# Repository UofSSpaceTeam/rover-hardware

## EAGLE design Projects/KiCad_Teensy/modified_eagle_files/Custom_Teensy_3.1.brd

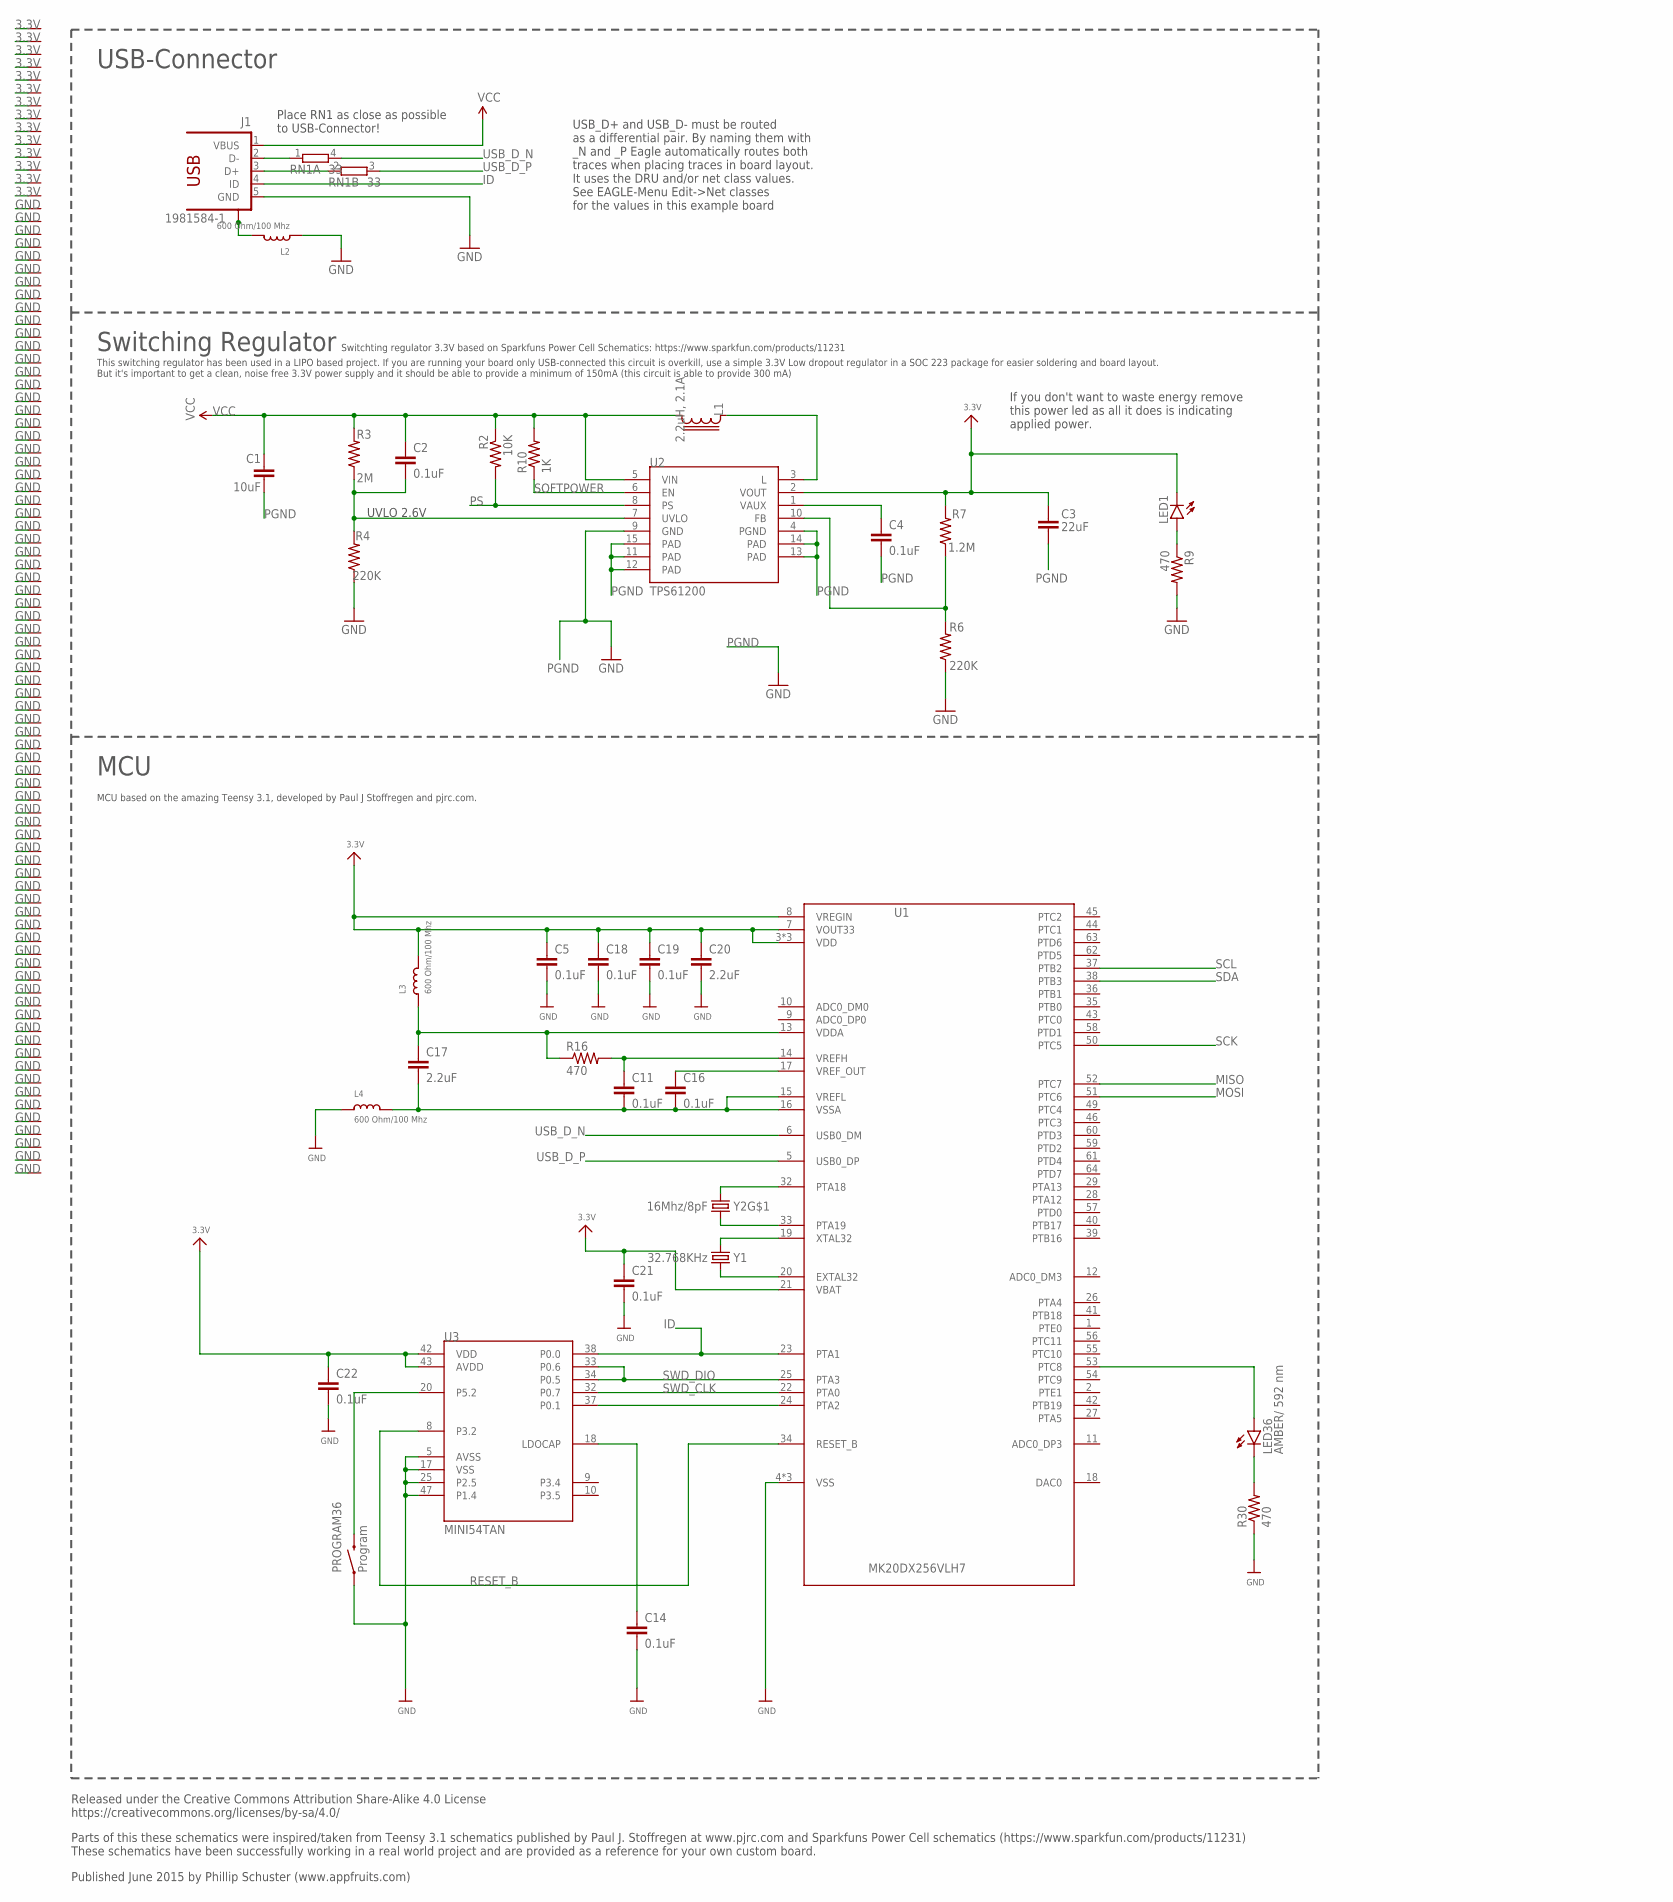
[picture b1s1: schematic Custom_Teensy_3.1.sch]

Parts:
C1: 10uF; 0603-CAP
C2, C4, C5, C11, C14, C16, C18, C19, C21, C22: 0.1uF; 0603-CAP
C3: 22uF; 0603-CAP
C17, C20: 2.2uF; 0603-CAP
J1: 1981584-1; MPN ZX62-AB-5PA(11)
L1: 2.2uH, 2.1A; LPS3015
L2, L3, L4: 600 Ohm/100 Mhz; 0805
LED1: LED-GREEN; LED-0603
LED36: AMBER/ 592 nm; LED-0603
PROGRAM36: Program; TACTILE-SWITCH-1101NE; MPN RS-282G05A3-SM RT
R2: 10K; 0603-RES
R3: 2M; 0603-RES
R4, R6: 220K; 0603-RES
R7: 1.2M; 0603-RES
R9, R16, R30: 470; 0603-RES
R10: 1K; 0603-RES
RN1: 33; EXB34V; MPN EXB-34V330JV
U1: MK20DX256VLH7; MPN MK20DX256VLH7
U2: TPS61200; QFN-10_PAD
U3: MINI54TAN
VP_0, VP_1, VP_2, VP_3, VP_4, VP_5, VP_6, VP_7, VP_8, VP_9, VP_10, VP_11, VP_12, VP_13, VP_23, VP_24, VP_25, VP_26, VP_27, VP_28, VP_29, VP_30, VP_31, VP_32, VP_33, VP_34, VP_35, VP_36, VP_37, VP_38, VP_39, VP_40, VP_41, VP_42, VP_43, VP_44, VP_45, VP_46, VP_47, VP_48, VP_49, VP_50, VP_51, VP_52, VP_53, VP_54, VP_55, VP_56, VP_57, VP_58, VP_59, VP_60, VP_61, VP_62, VP_63, VP_64, VP_65, VP_66, VP_67, VP_68, VP_69, VP_70, VP_71, VP_72, VP_73, VP_74, VP_75, VP_76, VP_77, VP_78, VP_79, VP_80, VP_81, VP_82, VP_83, VP_84, VP_85, VP_86, VP_87, VP_88, VP_89: VPDEV0; VPAC0
VP_14, VP_15, VP_16: VPDEV1; VPAC1
VP_17: VPDEV2; VPAC2
VP_18, VP_19, VP_20, VP_21, VP_22: VPDEV3; VPAC3
Y1: 32.768KHz; CRYSTAL-TXC-7A; MPN FC-255 32.7680K-A3
Y2: 16Mhz/8pF; CRYSTAL-SMD-5X3; MPN ECS-160-8-30B-CKM

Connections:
3.3V: C3.1, C5.1, C18.1, C19.1, C20.1, C21.1, C22.1, L3.2, LED1.C, R7.2, U1.3 (VDD), U1.7 (VOUT33), U1.8 (VREGIN), U1.21 (VBAT), U1.30 (VDD), U1.48 (VDD), U2.2 (VOUT), U3.42 (VDD), U3.43 (AVDD), VP_0.VP, VP_1.VP, VP_2.VP, VP_3.VP, VP_4.VP, VP_5.VP, VP_6.VP, VP_7.VP, VP_8.VP, VP_9.VP, VP_10.VP, VP_11.VP, VP_12.VP, VP_13.VP
FB: R6.2, R7.1, U2.10 (FB)
GND: C5.2, C14.2, C18.2, C19.2, C20.2, C21.2, C22.2, J1.5 (GND), L2.1, L4.1, PROGRAM36.P$1 (1), R4.1, R6.1, R9.2, R30.1, U1.4 (VSS), U1.31 (VSS), U1.47 (VSS), U3.5 (AVSS), U3.17 (VSS), U3.25 (P2.5), U3.47 (P1.4), VP_14.VP, VP_15.VP, VP_16.VP, VP_17.VP, VP_18.VP, VP_19.VP, VP_20.VP, VP_21.VP, VP_22.VP, VP_23.VP, VP_24.VP, VP_25.VP, VP_26.VP, VP_27.VP, VP_28.VP, VP_29.VP, VP_30.VP, VP_31.VP, VP_32.VP, VP_33.VP, VP_34.VP, VP_35.VP, VP_36.VP, VP_37.VP, VP_38.VP, VP_39.VP, VP_40.VP, VP_41.VP, VP_42.VP, VP_43.VP, VP_44.VP, VP_45.VP, VP_46.VP, VP_47.VP, VP_48.VP, VP_49.VP, VP_50.VP, VP_51.VP, VP_52.VP, VP_53.VP, VP_54.VP, VP_55.VP, VP_56.VP, VP_57.VP, VP_58.VP, VP_59.VP, VP_60.VP, VP_61.VP, VP_62.VP, VP_63.VP, VP_64.VP, VP_65.VP, VP_66.VP, VP_67.VP, VP_68.VP, VP_69.VP, VP_70.VP, VP_71.VP, VP_72.VP, VP_73.VP, VP_74.VP, VP_75.VP, VP_76.VP, VP_77.VP, VP_78.VP, VP_79.VP, VP_80.VP, VP_81.VP, VP_82.VP, VP_83.VP, VP_84.VP, VP_85.VP, VP_86.VP, VP_87.VP, VP_88.VP, VP_89.VP
ID: J1.4 (ID), U1.23 (PTA1), U3.38 (P0.0)
MISO: U1.52 (PTC7)
MOSI: U1.51 (PTC6)
unnamed: LED1.A, R9.1
unnamed: L1.1, U2.3 (L)
unnamed: LED36.A, U1.53 (PTC8)
unnamed: U1.24 (PTA2), U3.37 (P0.1)
unnamed: LED36.C, R30.2
unnamed: PROGRAM36.P$2 (2), U3.20 (P5.2)
unnamed: C14.1, U3.18 (LDOCAP)
unnamed: U1.32 (PTA18), Y2.3 (2)
unnamed: U1.33 (PTA19), Y2.1
unnamed: U1.19 (XTAL32), Y1.P$2 (2)
unnamed: U1.20 (EXTAL32), Y1.P$1 (1)
PGND: C1.2, C3.2, C4.2, U2.4 (PGND), U2.9 (GND), U2.11 (PAD), U2.12 (PAD), U2.13 (PAD), U2.14 (PAD), U2.15 (PAD)
PS: R2.2, U2.8 (PS)
RESET_B: U1.34 (RESET_B), U3.8 (P3.2)
SCK: U1.50 (PTC5)
SCL: U1.37 (PTB2)
SDA: U1.38 (PTB3)
SOFTPOWER: R10.1, U2.6 (EN)
SWD_CLK: U1.22 (PTA0), U3.32 (P0.7)
SWD_DIO: U1.25 (PTA3), U3.33 (P0.6), U3.34 (P0.5)
USB_CON_N: J1.2 (D-), RN1.1
USB_CON_P: J1.3 (D+), RN1.2 (1)
USB_D_N: RN1.4 (2), U1.6 (USB0_DM)
USB_D_P: RN1.3 (2), U1.5 (USB0_DP)
USB_SHIELD: J1.S1, J1.S2, J1.S3, J1.S4, L2.2
UVLO: C2.2, R3.1, R4.2, U2.7 (UVLO)
VAUX: C4.1, U2.1 (VAUX)
VCC: C1.1, C2.1, J1.1 (VBUS), L1.2, R2.1, R3.2, R10.2, U2.5 (VIN)
VDDA: C17.1, L3.1, R16.1, U1.13 (VDDA)
VREFH: C11.1, R16.2, U1.14 (VREFH)
VREFL: C11.2, C16.2, C17.2, L4.2, U1.15 (VREFL), U1.16 (VSSA)
VREF_OUT: C16.1, U1.17 (VREF_OUT)

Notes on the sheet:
UVLO 2.6V
USB-Connector
Switching Regulator
MCU
MCU based on the amazing Teensy 3.1, developed by Paul J Stoffregen and pjrc.com.
Place RN1 as close as possible to USB-Connector!
If you don't want to waste energy remove this power led as all it does is indicating applied power.
USB_D+ and USB_D- must be routed as a differential pair. By naming them with _N and _P Eagle automatically routes both traces when placing traces in board layout. It uses the DRU and/or net class values. See EAGLE-Menu Edit->Net classes for the values in this example board
Released under the Creative Commons Attribution Share-Alike 4.0 License https://creativecommons.org/licenses/by-sa/4.0/
Parts of this these schematics were inspired/taken from Teensy 3.1 schematics published by Paul J. Stoffregen at www.pjrc.com and Sparkfuns Power Cell schematics (https://www.sparkfun.com/products/11231) These schematics have been successfully working in a real world project and are provided as a r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
Published June 2015 by Phillip Schuster (www.appfruits.com)
Switchting regulator 3.3V based on Sparkfuns Power Cell Schematics: https://www.sparkfun.com/products/11231
This switching regulator has been used in a LIPO based project. If you are running your board only USB-connected this circuit is overkill, use a simple 3.3V Low dropout regulator in a SOC 223 package for easier soldering and board layout. But it's important to get a clean, noise free 3.3V power sup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

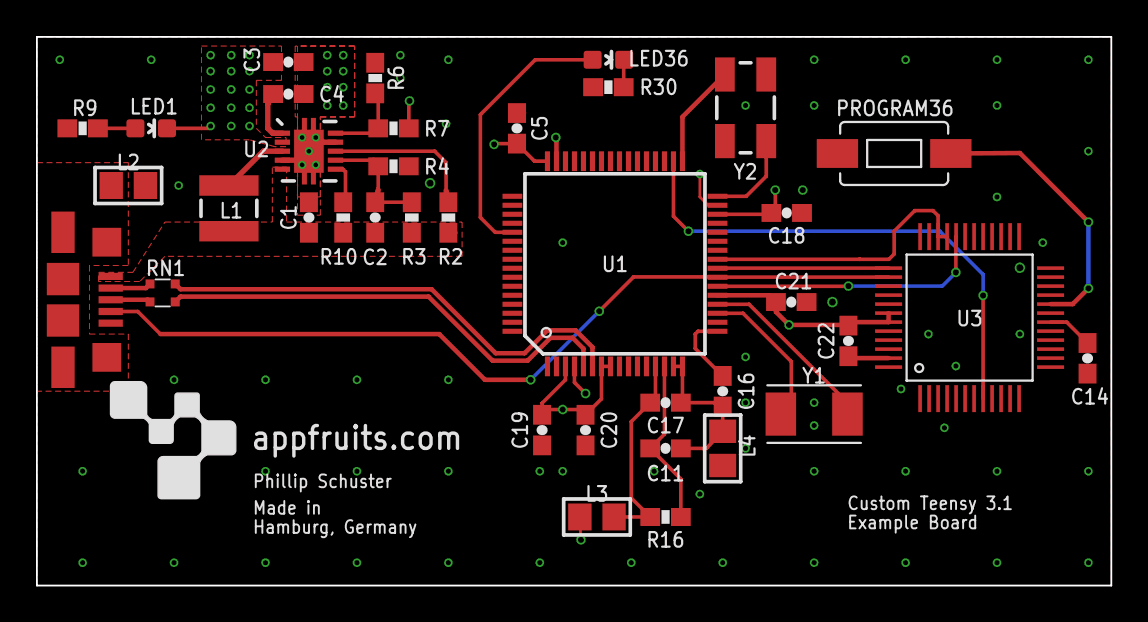
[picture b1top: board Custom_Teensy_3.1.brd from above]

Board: 4 copper layers, 59.7 x 30.5 mm, 127 parts (0 on the bottom side), 33 nets.

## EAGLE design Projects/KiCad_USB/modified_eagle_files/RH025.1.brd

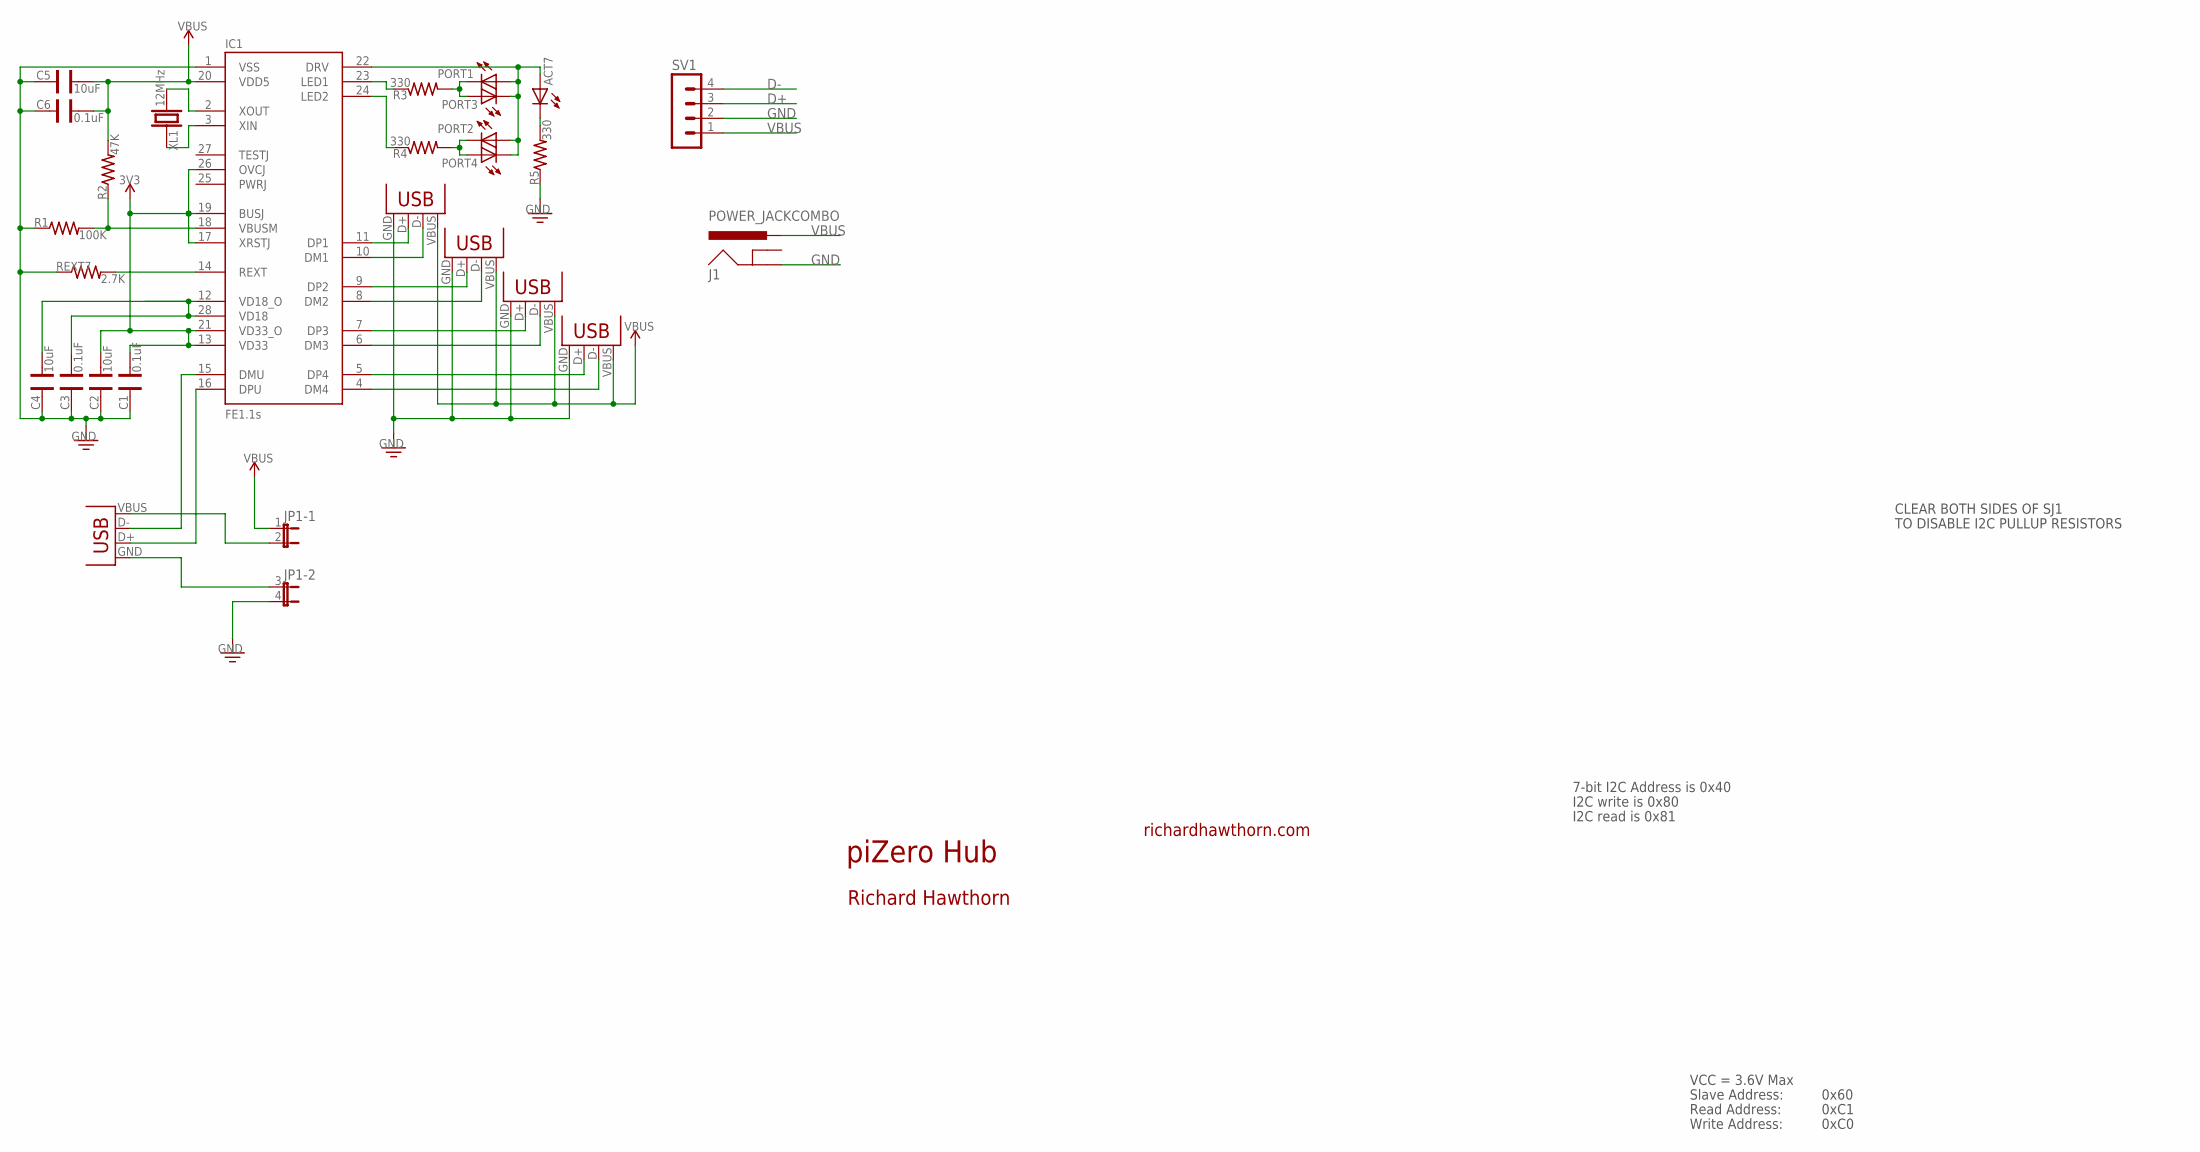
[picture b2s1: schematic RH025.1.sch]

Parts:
ACT7: LED0603; LED-0603
C1, C3, C6: 0.1uF; CAP-0603
C2, C4, C5: 10uF; CAP-0603
IC1: FE1.1S; FE1.1S_SSOP-28
J1: POWER_JACKCOMBO; POWER_JACK_COMBO
JP1: JP2QE; JP2Q
PORT1, PORT2, PORT3, PORT4: LED0603; LED-0603
R1: 100K; RES-0603
R2: 47K; RES-0603
R3, R4, R5: 330; RES-0603
REXT7: 2.7K; RES-0603
SV1: MA04-1
USB1: USBMICROB-PTH; USB-MICROB-TH
USB2, USB3, USB4, USB5: USBA-PTH; USB-A-F-PTH
XL1: 12MHz; HC49UP

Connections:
3V3: C1.1, C2.1, IC1.13 (VD33), IC1.17 (XRSTJ), IC1.19 (BUSJ), IC1.21 (VD33_O), IC1.26 (OVCJ)
D+: IC1.16 (DPU), SV1.3, USB1.D+
D-: IC1.15 (DMU), SV1.4, USB1.D-
GND: C1.2, C2.2, C3.2, C4.2, C5.2, C6.2, IC1.1 (VSS), J1.GND@1 (GND), JP1.4 (2), R1.1, R5.1, REXT7.1, SV1.2, USB2.GND, USB3.GND, USB4.GND, USB5.GND
unnamed: IC1.14 (REXT), REXT7.2
unnamed: JP1.2, USB1.VBUS
unnamed: JP1.3 (1), USB1.GND
unnamed: PORT2.C, PORT4.A, R4.2
unnamed: IC1.2 (XOUT), XL1.2
unnamed: C3.1, C4.1, IC1.12 (VD18_O), IC1.28 (VD18)
unnamed: IC1.3 (XIN), XL1.1
unnamed: IC1.11 (DP1), USB5.D+
unnamed: IC1.10 (DM1), USB5.D-
unnamed: IC1.18 (VBUSM), R1.2, R2.1
unnamed: IC1.9 (DP2), USB4.D+
unnamed: IC1.8 (DM2), USB4.D-
unnamed: IC1.7 (DP3), USB3.D+
unnamed: IC1.6 (DM3), USB3.D-
unnamed: IC1.5 (DP4), USB2.D+
unnamed: IC1.4 (DM4), USB2.D-
unnamed: PORT1.C, PORT3.A, R3.2
unnamed: ACT7.C, R5.2
unnamed: IC1.23 (LED1), R3.1
unnamed: IC1.24 (LED2), R4.1
unnamed: ACT7.A, IC1.22 (DRV), PORT1.A, PORT2.A, PORT3.C, PORT4.C
VBUS: C5.1, C6.1, IC1.20 (VDD5), J1.POWER (PWR), JP1.1, R2.2, SV1.1, USB2.VBUS, USB3.VBUS, USB4.VBUS, USB5.VBUS

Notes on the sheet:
piZero Hub
richardhawthorn.com
Richard Hawthorn
CLEAR BOTH SIDES OF SJ1
TO DISABLE I2C PULLUP RESISTORS
7-bit I2C Address is 0x40
I2C write is 0x80
I2C read is 0x81
VCC = 3.6V Max
Read Address:
Write Address:
Slave Address:
0x60
0xC1
0xC0

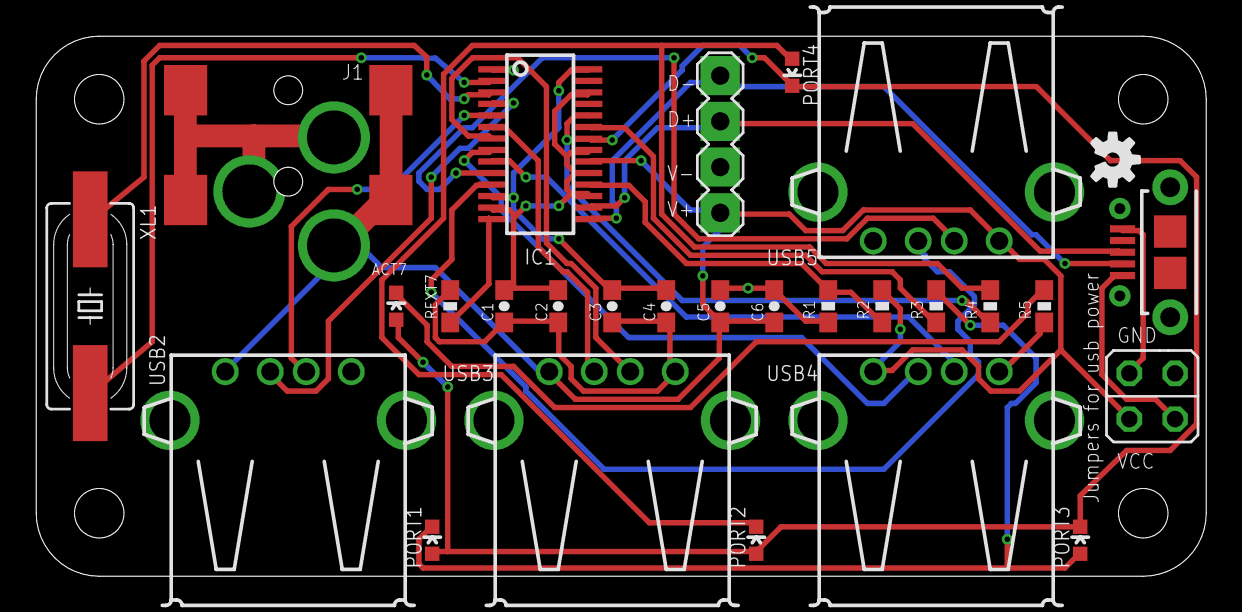
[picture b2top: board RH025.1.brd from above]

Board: 2 copper layers, 65.0 x 30.0 mm, 28 parts (0 on the bottom side), 26 nets.

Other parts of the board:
U$3: OSHW-LOGO-S

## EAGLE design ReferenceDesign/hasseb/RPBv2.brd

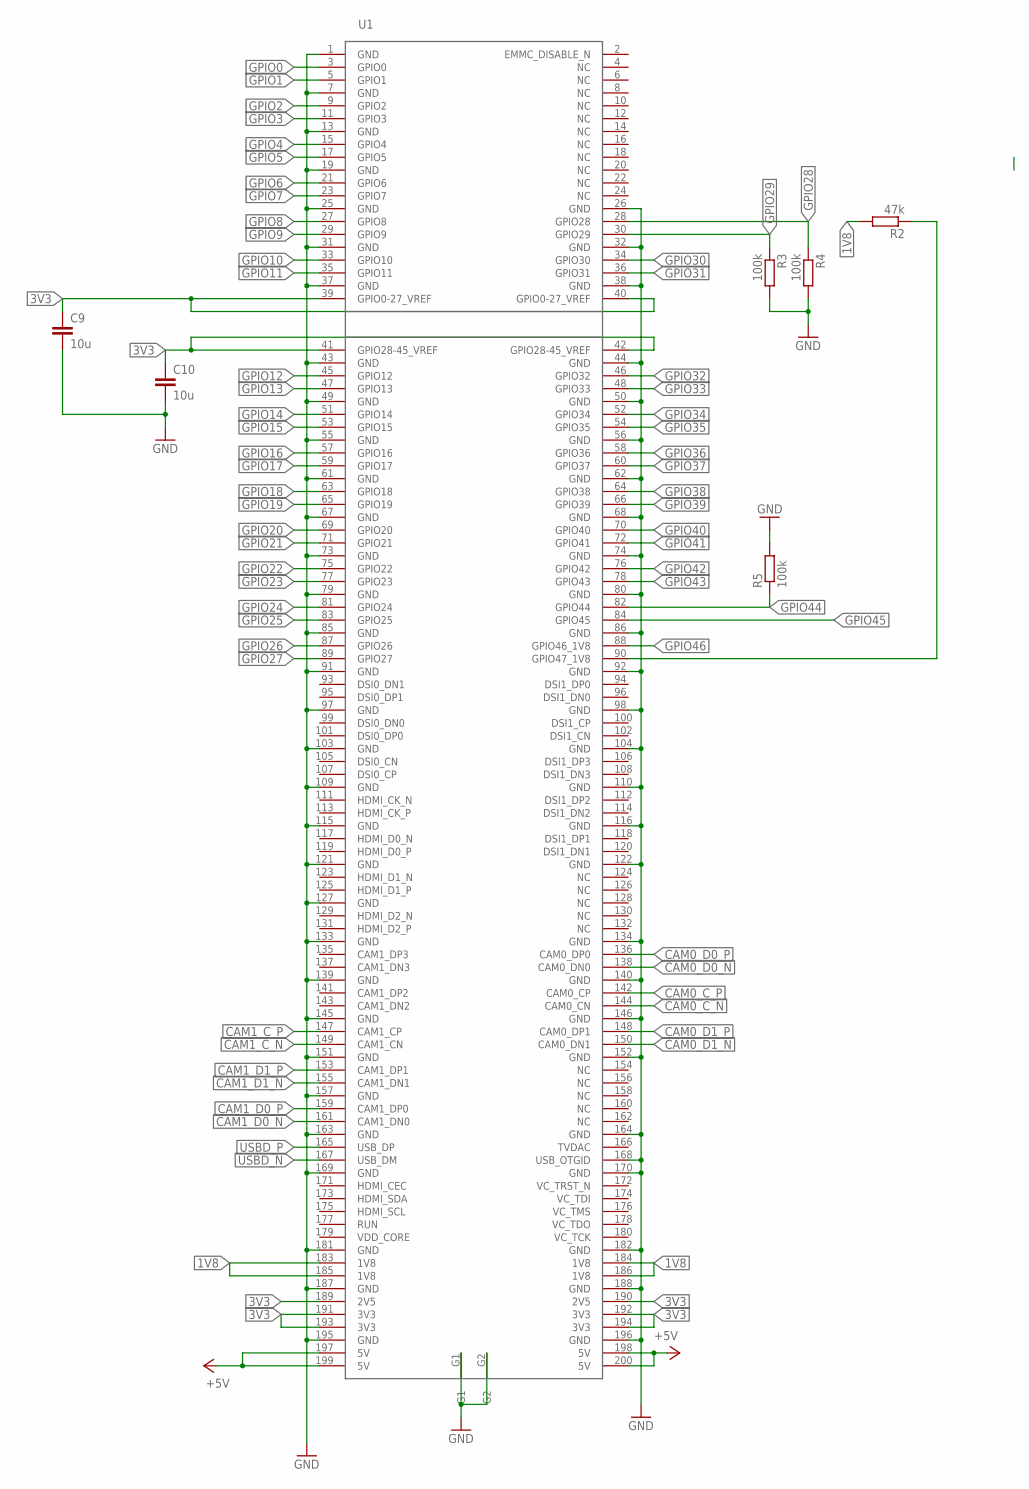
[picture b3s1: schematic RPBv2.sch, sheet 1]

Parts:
C9, C10: 10u; C0805
R2: 47k; R0603
R3, R4, R5: 100k; R0603
U1: RASPI; SO-DIMM

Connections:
1V8: R2.2, U1.183 (1V8), U1.184 (1V8), U1.185 (1V8), U1.186 (1V8); also elsewhere on the board
3V3: C9.1, C10.1, U1.39 (GPIO0-27_VREF), U1.40 (GPIO0-27_VREF), U1.41 (GPIO28-45_VREF), U1.42 (GPIO28-45_VREF), U1.189 (2V5), U1.190 (2V5), U1.191 (3V3), U1.192 (3V3), U1.193 (3V3), U1.194 (3V3); also elsewhere on the board
+5V: U1.197 (5V), U1.198 (5V), U1.199 (5V), U1.200 (5V); also elsewhere on the board
CAM0_C_N: U1.144 (CAM0_CN); also elsewhere on the board
CAM0_C_P: U1.142 (CAM0_CP); also elsewhere on the board
CAM0_D0_N: U1.138 (CAM0_DN0); also elsewhere on the board
CAM0_D0_P: U1.136 (CAM0_DP0); also elsewhere on the board
CAM0_D1_N: U1.150 (CAM0_DN1); also elsewhere on the board
CAM0_D1_P: U1.148 (CAM0_DP1); also elsewhere on the board
CAM1_C_N: U1.149 (CAM1_CN); also elsewhere on the board
CAM1_C_P: U1.147 (CAM1_CP); also elsewhere on the board
CAM1_D0_N: U1.161 (CAM1_DN0); also elsewhere on the board
CAM1_D0_P: U1.159 (CAM1_DP0); also elsewhere on the board
CAM1_D1_N: U1.155 (CAM1_DN1); also elsewhere on the board
CAM1_D1_P: U1.153 (CAM1_DP1); also elsewhere on the board
GND: C9.2, C10.2, R3.2, R4.2, R5.2, U1.1 (GND), U1.7 (GND), U1.13 (GND), U1.19 (GND), U1.25 (GND), U1.26 (GND), U1.31 (GND), U1.32 (GND), U1.37 (GND), U1.38 (GND), U1.43 (GND), U1.44 (GND), U1.49 (GND), U1.50 (GND), U1.55 (GND), U1.56 (GND), U1.61 (GND), U1.62 (GND), U1.67 (GND), U1.68 (GND), U1.73 (GND), U1.74 (GND), U1.79 (GND), U1.80 (GND), U1.85 (GND), U1.86 (GND), U1.91 (GND), U1.92 (GND), U1.97 (GND), U1.98 (GND), U1.103 (GND), U1.104 (GND), U1.109 (GND), U1.110 (GND), U1.115 (GND), U1.116 (GND), U1.121 (GND), U1.122 (GND), U1.127 (GND), U1.133 (GND), U1.134 (GND), U1.139 (GND), U1.140 (GND), U1.145 (GND), U1.146 (GND), U1.151 (GND), U1.152 (GND), U1.157 (GND), U1.163 (GND), U1.164 (GND), U1.168 (USB_OTGID), U1.169 (GND), U1.170 (GND), U1.181 (GND), U1.182 (GND), U1.187 (GND), U1.188 (GND), U1.195 (GND), U1.196 (GND), U1.G1, U1.G2; also elsewhere on the board
GPIO0: U1.3 (GPIO0); also elsewhere on the board
GPIO1: U1.5 (GPIO1); also elsewhere on the board
GPIO2: U1.9 (GPIO2); also elsewhere on the board
GPIO3: U1.11 (GPIO3); also elsewhere on the board
GPIO4: U1.15 (GPIO4); also elsewhere on the board
GPIO5: U1.17 (GPIO5); also elsewhere on the board
GPIO6: U1.21 (GPIO6); also elsewhere on the board
GPIO7: U1.23 (GPIO7); also elsewhere on the board
GPIO8: U1.27 (GPIO8); also elsewhere on the board
GPIO9: U1.29 (GPIO9); also elsewhere on the board
GPIO10: U1.33 (GPIO10); also elsewhere on the board
GPIO11: U1.35 (GPIO11); also elsewhere on the board
GPIO12: U1.45 (GPIO12); also elsewhere on the board
GPIO13: U1.47 (GPIO13); also elsewhere on the board
GPIO14: U1.51 (GPIO14); also elsewhere on the board
GPIO15: U1.53 (GPIO15); also elsewhere on the board
GPIO16: U1.57 (GPIO16); also elsewhere on the board
GPIO17: U1.59 (GPIO17); also elsewhere on the board
GPIO18: U1.63 (GPIO18); also elsewhere on the board
GPIO19: U1.65 (GPIO19); also elsewhere on the board
GPIO20: U1.69 (GPIO20); also elsewhere on the board
GPIO21: U1.71 (GPIO21); also elsewhere on the board
GPIO22: U1.75 (GPIO22); also elsewhere on the board
GPIO23: U1.77 (GPIO23); also elsewhere on the board
GPIO24: U1.81 (GPIO24); also elsewhere on the board
GPIO25: U1.83 (GPIO25); also elsewhere on the board
GPIO26: U1.87 (GPIO26); also elsewhere on the board
GPIO27: U1.89 (GPIO27); also elsewhere on the board
GPIO28: R4.1, U1.28 (GPIO28); also elsewhere on the board
GPIO29: R3.1, U1.30 (GPIO29); also elsewhere on the board
GPIO30: U1.34 (GPIO30); also elsewhere on the board
GPIO31: U1.36 (GPIO31); also elsewhere on the board
GPIO32: U1.46 (GPIO32)
GPIO33: U1.48 (GPIO33)
GPIO34: U1.52 (GPIO34)
GPIO35: U1.54 (GPIO35)
GPIO36: U1.58 (GPIO36)
GPIO37: U1.60 (GPIO37)
GPIO38: U1.64 (GPIO38)
GPIO39: U1.66 (GPIO39)
GPIO40: U1.70 (GPIO40)
GPIO41: U1.72 (GPIO41)
GPIO42: U1.76 (GPIO42)
GPIO43: U1.78 (GPIO43)
GPIO44: R5.1, U1.82 (GPIO44)
GPIO45: U1.84 (GPIO45)
GPIO46: U1.88 (GPIO46_1V8)
unnamed: R2.1, U1.90 (GPIO47_1V8)
USBD_N: U1.167 (USB_DM); also elsewhere on the board
USBD_P: U1.165 (USB_DP); also elsewhere on the board

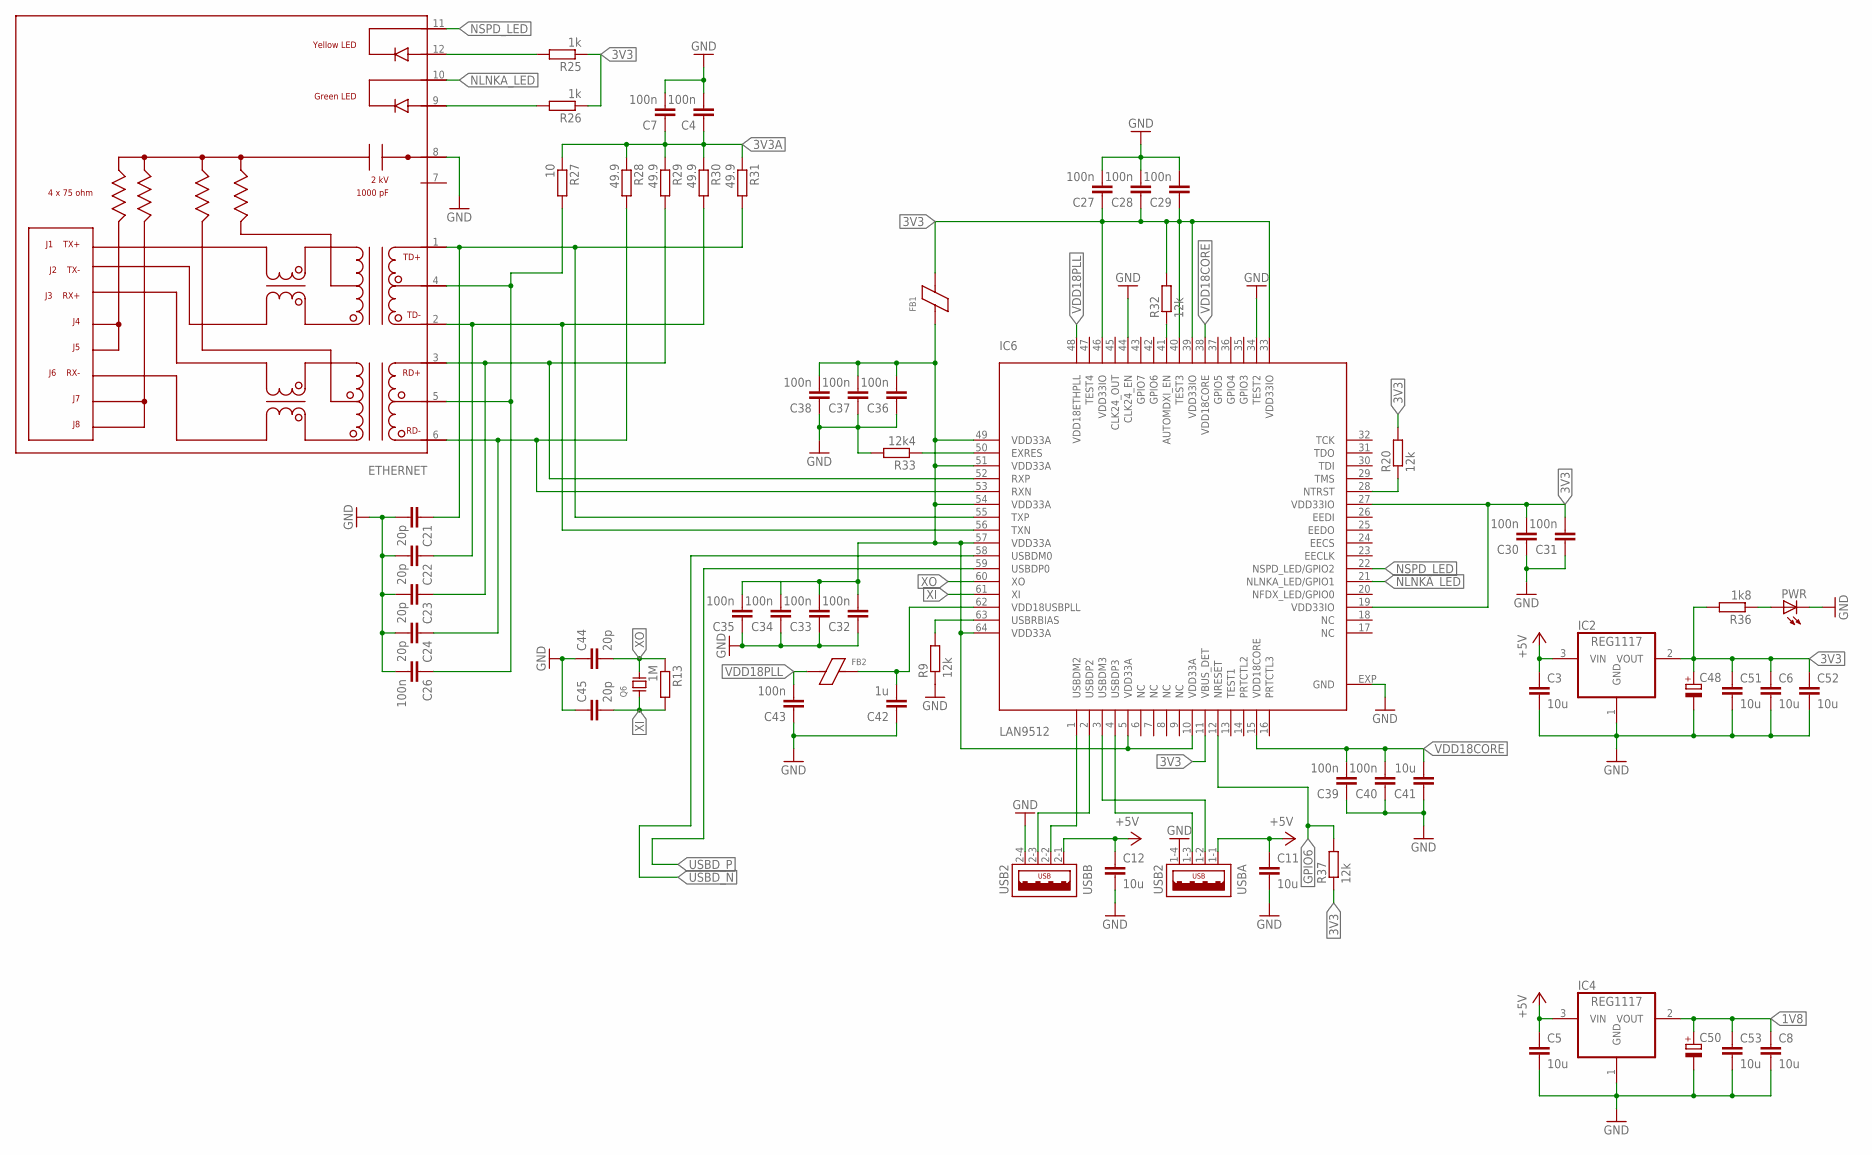
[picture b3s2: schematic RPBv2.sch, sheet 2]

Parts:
C3, C5, C6, C8, C11, C12, C41, C51, C52, C53: 10u; C0805
C4, C7, C26, C27, C28, C29, C30, C31, C32, C33, C34, C35, C36, C37, C38, C39, C40, C43: 100n; C0603
C21, C22, C23, C24, C44, C45: 20p; C0603
C42: 1u; C0805
C48, C50: CPOL-EU153CLV-0605; 153CLV-0605
ETHERNET: HR911105A; RJ45
FB1, FB2: FERRITE_BEAD; C0805
IC2, IC4: REG1117; SOT223
IC6: LAN9512; QFN64-9X9
PWR: LEDCHIP-LED0603; CHIP-LED0603
Q6: CTS_32X25_SMD; CTS_32X25
R9, R20, R32, R37: 12k; R0603
R13: 1M; R0603
R25, R26: 1k; R0603
R27: 10; R0603
R28, R29, R30, R31: 49.9; R0603
R33: 12k4; R0603
R36: 1k8; R0603
USB: USB2

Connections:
1V8: C8.1, C50.+, C53.1, IC4.2 (VOUT); also elsewhere on the board
3V3: C6.1, C27.1, C28.1, C29.1, C30.2, C31.2, C48.+, C51.1, C52.1, FB1.2, IC2.2 (VOUT), IC6.11 (VBUS_DET), IC6.19 (VDD33IO), IC6.27 (VDD33IO), IC6.33 (VDD33IO), IC6.39 (VDD33IO), IC6.40 (TEST3), IC6.46 (VDD33IO), R20.2, R25.1, R26.1, R32.2, R36.2, R37.1; also elsewhere on the board
3V3A: C4.1, C7.1, C32.2, C33.2, C34.2, C35.2, C36.2, C37.2, C38.2, FB1.1, IC6.5 (VDD33A), IC6.10 (VDD33A), IC6.49 (VDD33A), IC6.51 (VDD33A), IC6.54 (VDD33A), IC6.57 (VDD33A), IC6.64 (VDD33A), R27.1, R28.1, R29.1, R30.1, R31.1
+5V: C3.1, C5.1, C11.1, C12.1, IC2.3 (VIN), IC4.3 (VIN), USB.1-1 (1), USB.2-1 (1); also elsewhere on the board
GND: C3.2, C4.2, C5.2, C6.2, C7.2, C8.2, C11.2, C12.2, C21.2, C22.2, C23.2, C24.2, C26.2, C27.2, C28.2, C29.2, C30.1, C31.1, C32.1, C33.1, C34.1, C35.1, C36.1, C37.1, C38.1, C39.1, C40.1, C41.1, C42.1, C43.1, C44.1, C45.1, C48.-, C50.-, C51.2, C52.2, C53.2, ETHERNET.8, IC2.1 (GND), IC4.1 (GND), IC6.34 (TEST2), IC6.44 (CLK24_EN), IC6.EXP (GND), PWR.C, R9.1, R33.2, USB.1-4 (4), USB.2-4 (4); also elsewhere on the board
GPIO6: IC6.12 (NRESET), R37.2; also elsewhere on the board
unnamed: PWR.A, R36.1
unnamed: ETHERNET.12, R25.2
unnamed: ETHERNET.9, R26.2
unnamed: IC6.28 (NTRST), R20.1
unnamed: IC6.63 (USBRBIAS), R9.2
unnamed: C26.1, ETHERNET.4, ETHERNET.5, R27.2
unnamed: C42.2, FB2.2, IC6.62 (VDD18USBPLL)
unnamed: IC6.41 (AUTOMDXI_EN), R32.1
unnamed: IC6.50 (EXRES), R33.1
NLNKA_LED: ETHERNET.10, IC6.21 (NLNKA_LED/GPIO1)
NSPD_LED: ETHERNET.11, IC6.22 (NSPD_LED/GPIO2)
RX_N: C24.1, ETHERNET.6, IC6.53 (RXN), R28.2
RX_P: C23.1, ETHERNET.3, IC6.52 (RXP), R29.2
TX_N: C22.1, ETHERNET.2, IC6.56 (TXN), R30.2
TX_P: C21.1, ETHERNET.1, IC6.55 (TXP), R31.2
USBD2_N: IC6.1 (USBDM2), USB.2-2 (2)
USBD2_P: IC6.2 (USBDP2), USB.2-3 (3)
USBD3_N: IC6.3 (USBDM3), USB.1-2 (2)
USBD3_P: IC6.4 (USBDP3), USB.1-3 (3)
USBD_N: IC6.58 (USBDM0); also elsewhere on the board
USBD_P: IC6.59 (USBDP0); also elsewhere on the board
VDD18CORE: C39.2, C40.2, C41.2, IC6.15 (VDD18CORE), IC6.38 (VDD18CORE)
VDD18PLL: C43.2, FB2.1, IC6.48 (VDD18ETHPLL)
XI: C45.2, IC6.61 (XI), Q6.1 (X1), R13.2
XO: C44.2, IC6.60 (XO), Q6.3 (X2), R13.1

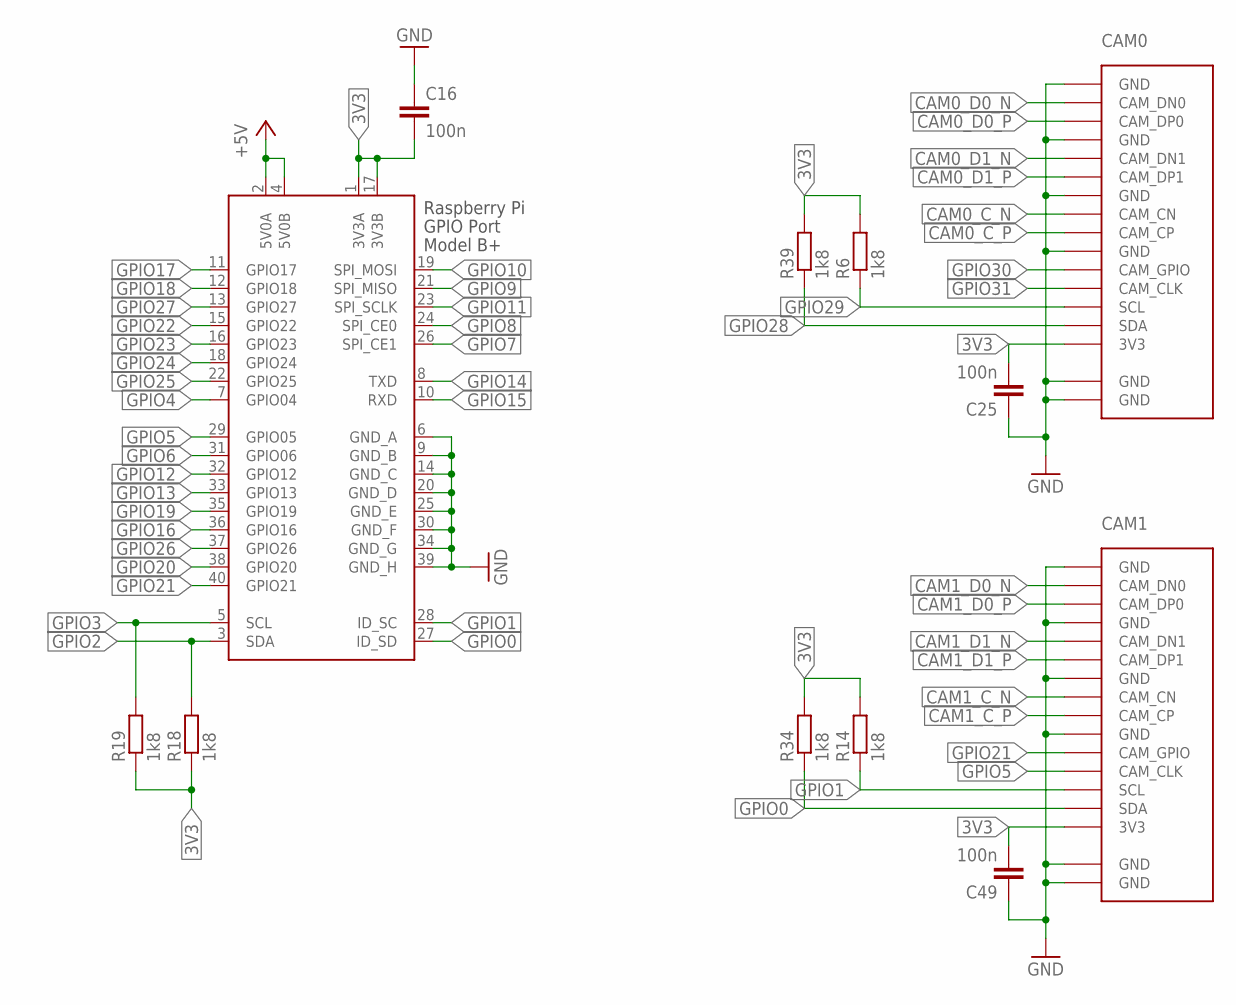
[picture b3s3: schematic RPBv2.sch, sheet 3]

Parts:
C16, C25, C49: 100n; C0603
CAM0: FFC-15
CAM1: RASPI_CAM; FFC-15
GPIO: PITFT_; RASPI_GPIO_B+_PIN
R6, R14, R18, R19, R34, R39: 1k8; R0603

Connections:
3V3: C16.2, C25.2, C49.2, CAM0.P$15 (3V3), CAM1.P$15 (3V3), GPIO.1 (3V3A), GPIO.17 (3V3B), R6.2, R14.2, R18.1, R19.1, R34.2, R39.2; also elsewhere on the board
+5V: GPIO.2 (5V0A), GPIO.4 (5V0B); also elsewhere on the board
CAM0_C_N: CAM0.P$8 (CAM_CN); also elsewhere on the board
CAM0_C_P: CAM0.P$9 (CAM_CP); also elsewhere on the board
CAM0_D0_N: CAM0.P$2 (CAM_DN0); also elsewhere on the board
CAM0_D0_P: CAM0.P$3 (CAM_DP0); also elsewhere on the board
CAM0_D1_N: CAM0.P$5 (CAM_DN1); also elsewhere on the board
CAM0_D1_P: CAM0.P$6 (CAM_DP1); also elsewhere on the board
CAM1_C_N: CAM1.P$8 (CAM_CN); also elsewhere on the board
CAM1_C_P: CAM1.P$9 (CAM_CP); also elsewhere on the board
CAM1_D0_N: CAM1.P$2 (CAM_DN0); also elsewhere on the board
CAM1_D0_P: CAM1.P$3 (CAM_DP0); also elsewhere on the board
CAM1_D1_N: CAM1.P$5 (CAM_DN1); also elsewhere on the board
CAM1_D1_P: CAM1.P$6 (CAM_DP1); also elsewhere on the board
GND: C16.1, C25.1, C49.1, CAM0.P$1 (GND), CAM0.P$4 (GND), CAM0.P$7 (GND), CAM0.P$10 (GND), CAM0.P$16 (GND), CAM0.P$17 (GND), CAM1.P$1 (GND), CAM1.P$4 (GND), CAM1.P$7 (GND), CAM1.P$10 (GND), CAM1.P$16 (GND), CAM1.P$17 (GND), GPIO.6 (GND_A), GPIO.9 (GND_B), GPIO.14 (GND_C), GPIO.20 (GND_D), GPIO.25 (GND_E), GPIO.30 (GND_F), GPIO.34 (GND_G), GPIO.39 (GND_H); also elsewhere on the board
GPIO0: CAM1.P$14 (SDA), GPIO.27 (ID_SD), R34.1; also elsewhere on the board
GPIO1: CAM1.P$13 (SCL), GPIO.28 (ID_SC), R14.1; also elsewhere on the board
GPIO2: GPIO.3 (SDA), R18.2; also elsewhere on the board
GPIO3: GPIO.5 (SCL), R19.2; also elsewhere on the board
GPIO4: GPIO.7 (GPIO04); also elsewhere on the board
GPIO5: CAM1.P$12 (CAM_CLK), GPIO.29 (GPIO05); also elsewhere on the board
GPIO6: GPIO.31 (GPIO06); also elsewhere on the board
GPIO7: GPIO.26 (SPI_CE1); also elsewhere on the board
GPIO8: GPIO.24 (SPI_CE0); also elsewhere on the board
GPIO9: GPIO.21 (SPI_MISO); also elsewhere on the board
GPIO10: GPIO.19 (SPI_MOSI); also elsewhere on the board
GPIO11: GPIO.23 (SPI_SCLK); also elsewhere on the board
GPIO12: GPIO.32 (GPIO12); also elsewhere on the board
GPIO13: GPIO.33 (GPIO13); also elsewhere on the board
GPIO14: GPIO.8 (TXD); also elsewhere on the board
GPIO15: GPIO.10 (RXD); also elsewhere on the board
GPIO16: GPIO.36 (GPIO16); also elsewhere on the board
GPIO17: GPIO.11 (GPIO17); also elsewhere on the board
GPIO18: GPIO.12 (GPIO18); also elsewhere on the board
GPIO19: GPIO.35 (GPIO19); also elsewhere on the board
GPIO20: GPIO.38 (GPIO20); also elsewhere on the board
GPIO21: CAM1.P$11 (CAM_GPIO), GPIO.40 (GPIO21); also elsewhere on the board
GPIO22: GPIO.15 (GPIO22); also elsewhere on the board
GPIO23: GPIO.16 (GPIO23); also elsewhere on the board
GPIO24: GPIO.18 (GPIO24); also elsewhere on the board
GPIO25: GPIO.22 (GPIO25); also elsewhere on the board
GPIO26: GPIO.37 (GPIO26); also elsewhere on the board
GPIO27: GPIO.13 (GPIO27); also elsewhere on the board
GPIO28: CAM0.P$14 (SDA), R39.1; also elsewhere on the board
GPIO29: CAM0.P$13 (SCL), R6.1; also elsewhere on the board
GPIO30: CAM0.P$11 (CAM_GPIO); also elsewhere on the board
GPIO31: CAM0.P$12 (CAM_CLK); also elsewhere on the board

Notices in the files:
Projects/KiCad_Teensy/modified_eagle_files/Custom_Teensy_3.1.brd:
to use/see all necessary layers. EAGLEs hobbyist license will do the trick.
Projects/KiCad_USB/modified_eagle_files/RH025.1.brd:
This work is licensed under the Creative Commons Attribution-ShareAlike 4.0 International License.
To view a copy of this license, visit http://creativecommons.org/licenses/by-sa/4.0
parts and their libraries:
SparkFun-Electromechanical: Licensing: Creative Commons ShareAlike 4.0 International - https://creativecommons.org/licenses/by-sa/4.0
con-usb: Copyright (C) 2008, Bob Starr
